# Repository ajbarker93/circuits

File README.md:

# circuits

A repository of printed circuit boards designed using KiCad.

LIAD: a PCB mount for ultra-violet LEDs. Intended use: illumination of a magneto-optical trap chamber to boost vapour pressure.

NI-SCSI: a digitally-isolated breakout for a National Instruments SCSI connector to generate 4x8 data lines for serial communication. Each block of 8 digital lines is combined with a regulated voltage source.

Urukul: a PCB to convert TTL digital signals into LVDS signals for compatibility with the Sinara Urukul DDS board (https://github.com/sinara-hw/Urukul/wiki).

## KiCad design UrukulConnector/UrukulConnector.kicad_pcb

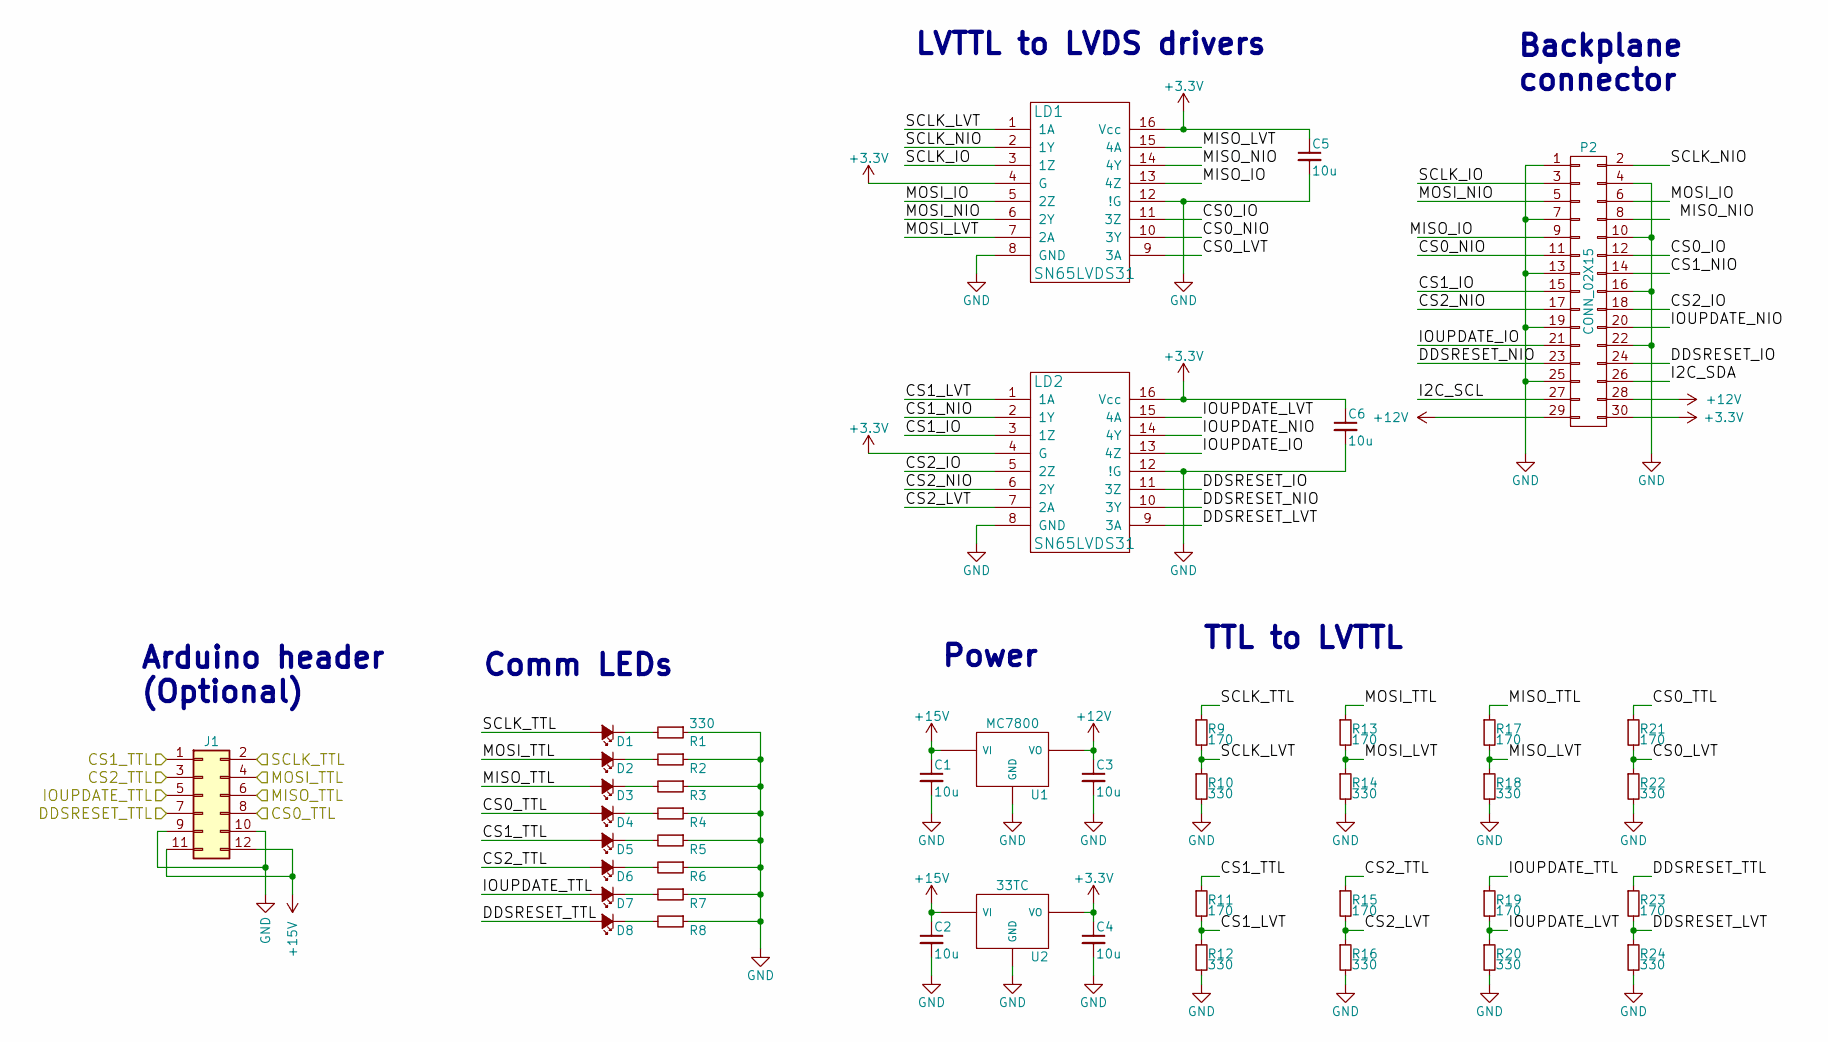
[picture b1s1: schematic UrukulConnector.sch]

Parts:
C1, C2, C3, C4, C5, C6: 10u; C_1206_HandSoldering
D1, D2, D3, D4, D5, D6, D7, D8: Led_Small; R_0805_HandSoldering
J1: Conn_02x06_Odd_Even; Pin_Header_Straight_2x06_Pitch2.54mm
LD1, LD2: SN65LVDS31; SOIC-16_3.9x9.9mm_Pitch1.27mm
P2: CONN_02X15; Pin_Header_Straight_2x15_Pitch2.54mm
R1, R2, R3, R4, R5, R6, R7, R8, R10, R12, R14, R16, R18, R20, R22, R24: 330; R_0805_HandSoldering
R9, R11, R13, R15, R17, R19, R21, R23: 170; R_0805_HandSoldering
U1: MC7800; TO-252-2
U2: 33TC; TO-252-2

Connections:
+3V3: C4.1, C5.1, C6.1, LD1.4 (G), LD1.16 (Vcc), LD2.4 (G), LD2.16 (Vcc), P2.30, U2.2 (VO)
+12V: C3.1, P2.28, P2.29, U1.3 (VO)
+15V: C1.1, C2.1, J1.11, J1.12, U1.1 (VI), U2.3 (VI)
/CS0_IO: LD1.11 (3Z), P2.12
/CS0_LVT: LD1.9 (3A), R21.2, R22.1
/CS0_NIO: LD1.10 (3Y), P2.11
/CS0_TTL: D4.2 (A), J1.8, R21.1
/CS1_IO: LD2.3 (1Z), P2.15
/CS1_LVT: LD2.1 (1A), R11.2, R12.1
/CS1_NIO: LD2.2 (1Y), P2.14
/CS1_TTL: D5.2 (A), J1.1, R11.1
/CS2_IO: LD2.5 (2Z), P2.18
/CS2_LVT: LD2.7 (2A), R15.2, R16.1
/CS2_NIO: LD2.6 (2Y), P2.17
/CS2_TTL: D6.2 (A), J1.3, R15.1
/DDSRESET_IO: LD2.11 (3Z), P2.24
/DDSRESET_LVT: LD2.9 (3A), R23.2, R24.1
/DDSRESET_NIO: LD2.10 (3Y), P2.23
/DDSRESET_TTL: D8.2 (A), J1.7, R23.1
/I2C_SCL: P2.27
/I2C_SDA: P2.26
/IOUPDATE_IO: LD2.13 (4Z), P2.21
/IOUPDATE_LVT: LD2.15 (4A), R19.2, R20.1
/IOUPDATE_NIO: LD2.14 (4Y), P2.20
/IOUPDATE_TTL: D7.2 (A), J1.5, R19.1
/MISO_IO: LD1.13 (4Z)
/MISO_LVT: LD1.15 (4A), R17.2, R18.1
/MISO_NIO: LD1.14 (4Y)
/MISO_TTL: D3.2 (A), J1.6, R17.1
/MOSI_IO: LD1.5 (2Z), P2.6
/MOSI_LVT: LD1.7 (2A), R13.2, R14.1
/MOSI_NIO: LD1.6 (2Y), P2.5
/MOSI_TTL: D2.2 (A), J1.4, R13.1
/SCLK_IO: LD1.3 (1Z), P2.3
/SCLK_LVT: LD1.1 (1A), R9.2, R10.1
/SCLK_NIO: LD1.2 (1Y), P2.2
/SCLK_TTL: D1.2 (A), J1.2, R9.1
GND: C1.2, C2.2, C3.2, C4.2, C5.2, C6.2, J1.9, J1.10, LD1.8 (GND), LD1.12 (!G), LD2.8 (GND), LD2.12 (!G), P2.1, P2.4, P2.7, P2.10, P2.13, P2.16, P2.19, P2.22, P2.25, R1.1, R2.1, R3.1, R4.1, R5.1, R6.1, R7.1, R8.1, R10.2, R12.2, R14.2, R16.2, R18.2, R20.2, R22.2, R24.2, U1.2 (GND), U2.1 (GND)
unnamed: D1.1 (K), R1.2
unnamed: D2.1 (K), R2.2
unnamed: D3.1 (K), R3.2
unnamed: D4.1 (K), R4.2
unnamed: D5.1 (K), R5.2
unnamed: D6.1 (K), R6.2
unnamed: D7.1 (K), R7.2
unnamed: D8.1 (K), R8.2

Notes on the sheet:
Backplane connector
LVTTL to LVDS drivers
Arduino header (Optional)
Power
TTL to LVTTL
Comm LEDs

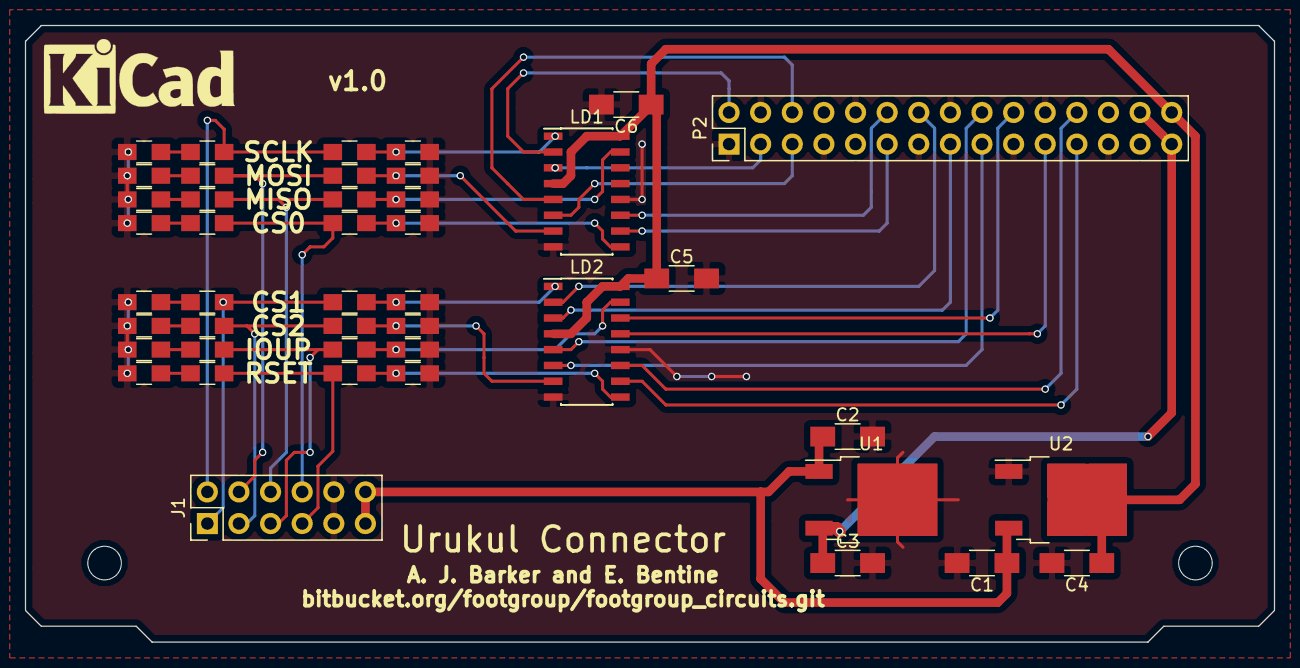
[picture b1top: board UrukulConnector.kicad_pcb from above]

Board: 2 copper layers, 100.3 x 49.5 mm, 44 parts (0 on the bottom side), 42 nets.

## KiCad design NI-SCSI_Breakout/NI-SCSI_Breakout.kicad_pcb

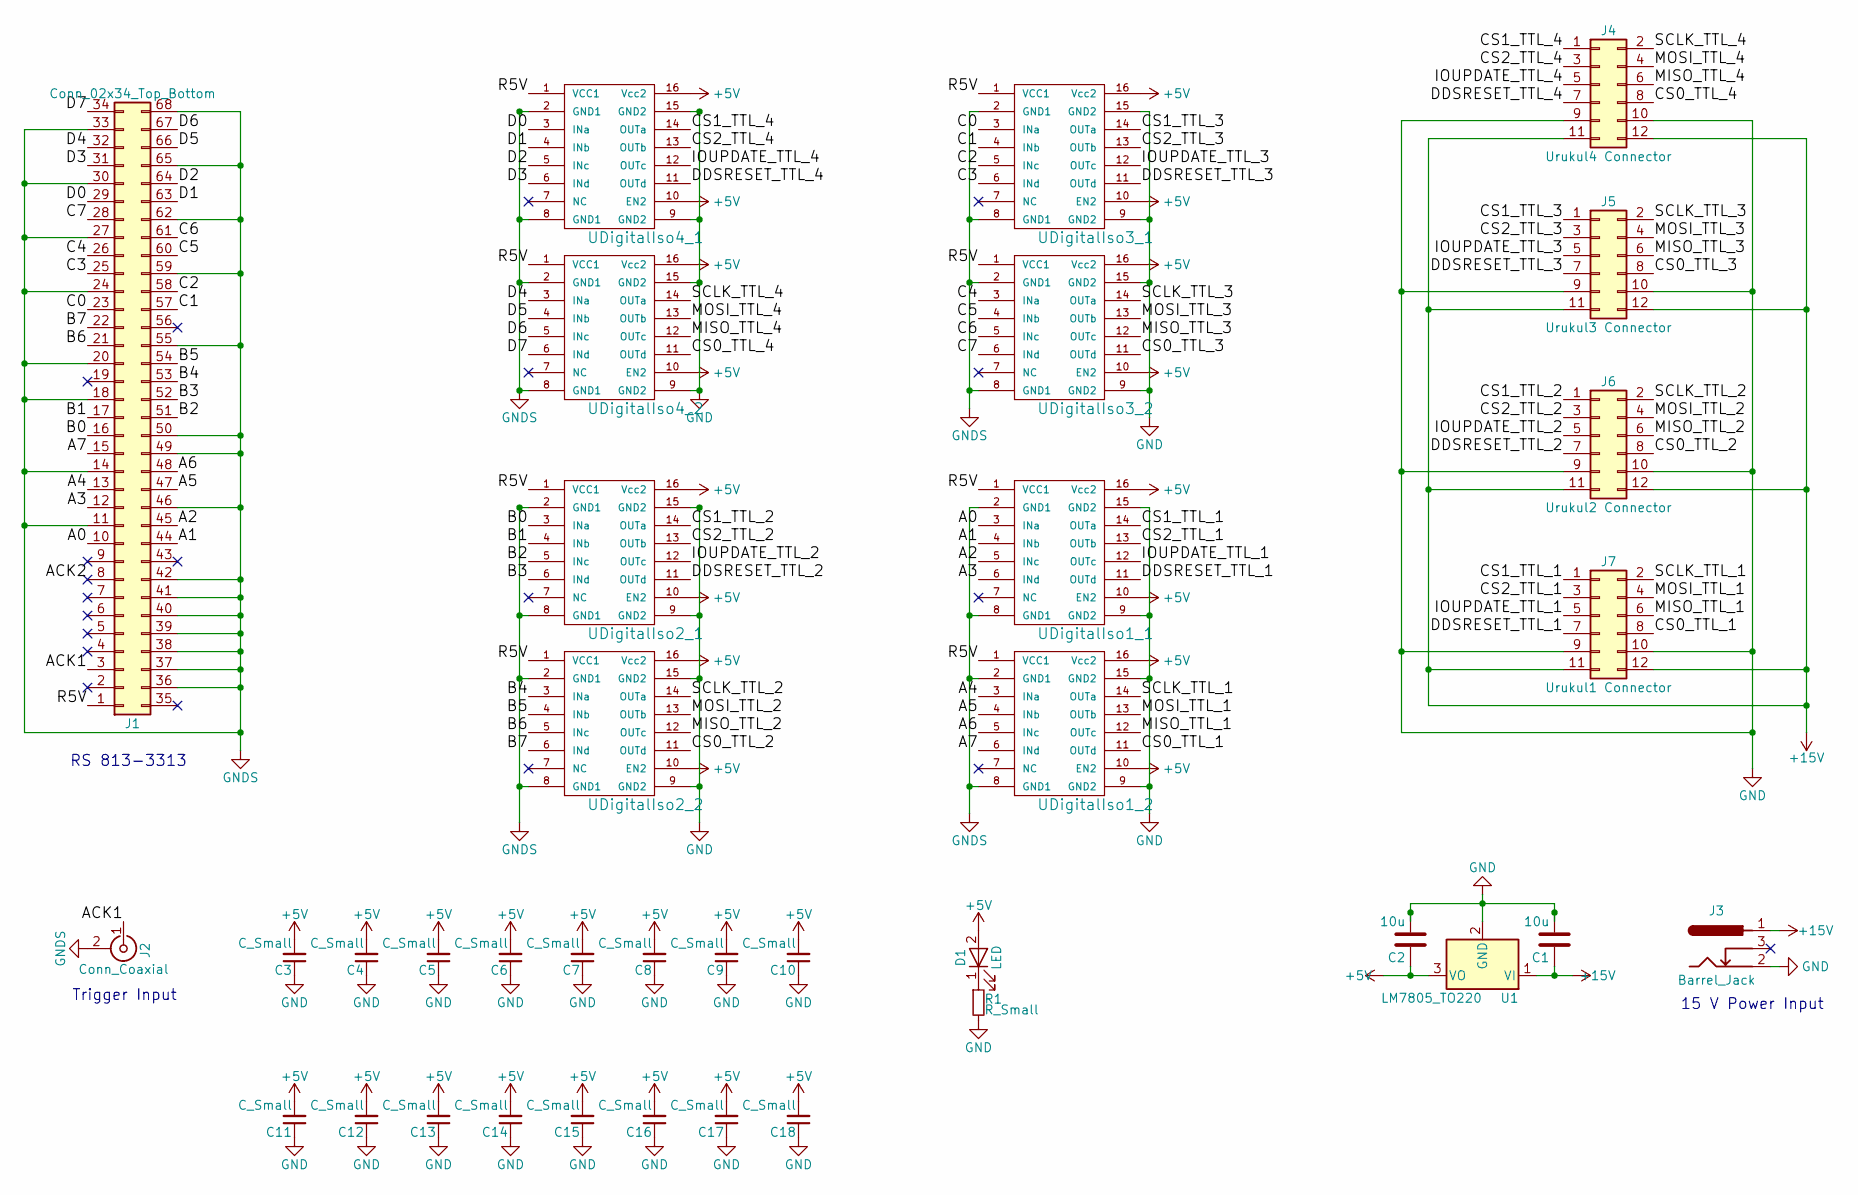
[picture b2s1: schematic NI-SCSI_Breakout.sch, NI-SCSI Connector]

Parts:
C1, C2: 10u; C_0805
C3, C4, C5, C6, C7, C8, C9, C10, C11, C12, C13, C14, C15, C16, C17, C18: C_Small; C_0805_HandSoldering
D1: LED; LED_0805_HandSoldering
J1: Conn_02x34_Top_Bottom; MH_SCSI_68_2.54mm
J2: Conn_Coaxial; SMA_THT_Jack_Straight
J3: Barrel_Jack; Barrel_Jack_CUI_PJ-102AH
J4: Urukul4 Connector; Pin_Header_Straight_2x06_Pitch2.54mm
J5: Urukul3 Connector; Pin_Header_Straight_2x06_Pitch2.54mm
J6: Urukul2 Connector; Pin_Header_Straight_2x06_Pitch2.54mm
J7: Urukul1 Connector; Pin_Header_Straight_2x06_Pitch2.54mm
R1: R_Small; LED_0805_HandSoldering
U1: LM7805_TO220; TO-252-2
UDigitalIso1_1, UDigitalIso1_2, UDigitalIso2_1, UDigitalIso2_2, UDigitalIso3_1, UDigitalIso3_2, UDigitalIso4_1, UDigitalIso4_2: ISO7741FQDWQ1; SOIC-16W_7.5x10.3mm_Pitch1.27mm

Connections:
+5V: C2.1, C3.2, C4.2, C5.2, C6.2, C7.2, C8.2, C9.2, C10.2, C11.2, C12.2, C13.2, C14.2, C15.2, C16.2, C17.2, C18.2, D1.2 (A), U1.3 (VO), UDigitalIso1_1.10 (EN2), UDigitalIso1_1.16 (Vcc2), UDigitalIso1_2.10 (EN2), UDigitalIso1_2.16 (Vcc2), UDigitalIso2_1.10 (EN2), UDigitalIso2_1.16 (Vcc2), UDigitalIso2_2.10 (EN2), UDigitalIso2_2.16 (Vcc2), UDigitalIso3_1.10 (EN2), UDigitalIso3_1.16 (Vcc2), UDigitalIso3_2.10 (EN2), UDigitalIso3_2.16 (Vcc2), UDigitalIso4_1.10 (EN2), UDigitalIso4_1.16 (Vcc2), UDigitalIso4_2.10 (EN2), UDigitalIso4_2.16 (Vcc2)
+15V: C1.1, J3.1, J4.11, J4.12, J5.11, J5.12, J6.11, J6.12, J7.11, J7.12, U1.1 (VI)
/A0: J1.10, UDigitalIso1_1.3 (INa)
/A1: J1.44, UDigitalIso1_1.4 (INb)
/A2: J1.45, UDigitalIso1_1.5 (INc)
/A3: J1.12, UDigitalIso1_1.6 (INd)
/A4: J1.13, UDigitalIso1_2.3 (INa)
/A5: J1.47, UDigitalIso1_2.4 (INb)
/A6: J1.48, UDigitalIso1_2.5 (INc)
/A7: J1.15, UDigitalIso1_2.6 (INd)
/ACK1: J1.3, J2.1 (In)
/ACK2: J1.8
/B0: J1.16, UDigitalIso2_1.3 (INa)
/B1: J1.17, UDigitalIso2_1.4 (INb)
/B2: J1.51, UDigitalIso2_1.5 (INc)
/B3: J1.52, UDigitalIso2_1.6 (INd)
/B4: J1.53, UDigitalIso2_2.3 (INa)
/B5: J1.54, UDigitalIso2_2.4 (INb)
/B6: J1.21, UDigitalIso2_2.5 (INc)
/B7: J1.22, UDigitalIso2_2.6 (INd)
/C0: J1.23, UDigitalIso3_1.3 (INa)
/C1: J1.57, UDigitalIso3_1.4 (INb)
/C2: J1.58, UDigitalIso3_1.5 (INc)
/C3: J1.25, UDigitalIso3_1.6 (INd)
/C4: J1.26, UDigitalIso3_2.3 (INa)
/C5: J1.60, UDigitalIso3_2.4 (INb)
/C6: J1.61, UDigitalIso3_2.5 (INc)
/C7: J1.28, UDigitalIso3_2.6 (INd)
/CS0_TTL_1: J7.8, UDigitalIso1_2.11 (OUTd)
/CS0_TTL_2: J6.8, UDigitalIso2_2.11 (OUTd)
/CS0_TTL_3: J5.8, UDigitalIso3_2.11 (OUTd)
/CS0_TTL_4: J4.8, UDigitalIso4_2.11 (OUTd)
/CS1_TTL_1: J7.1, UDigitalIso1_1.14 (OUTa)
/CS1_TTL_2: J6.1, UDigitalIso2_1.14 (OUTa)
/CS1_TTL_3: J5.1, UDigitalIso3_1.14 (OUTa)
/CS1_TTL_4: J4.1, UDigitalIso4_1.14 (OUTa)
/CS2_TTL_1: J7.3, UDigitalIso1_1.13 (OUTb)
/CS2_TTL_2: J6.3, UDigitalIso2_1.13 (OUTb)
/CS2_TTL_3: J5.3, UDigitalIso3_1.13 (OUTb)
/CS2_TTL_4: J4.3, UDigitalIso4_1.13 (OUTb)
/D0: J1.29, UDigitalIso4_1.3 (INa)
/D1: J1.63, UDigitalIso4_1.4 (INb)
/D2: J1.64, UDigitalIso4_1.5 (INc)
/D3: J1.31, UDigitalIso4_1.6 (INd)
/D4: J1.32, UDigitalIso4_2.3 (INa)
/D5: J1.66, UDigitalIso4_2.4 (INb)
/D6: J1.67, UDigitalIso4_2.5 (INc)
/D7: J1.34, UDigitalIso4_2.6 (INd)
/DDSRESET_TTL_1: J7.7, UDigitalIso1_1.11 (OUTd)
/DDSRESET_TTL_2: J6.7, UDigitalIso2_1.11 (OUTd)
/DDSRESET_TTL_3: J5.7, UDigitalIso3_1.11 (OUTd)
/DDSRESET_TTL_4: J4.7, UDigitalIso4_1.11 (OUTd)
/IOUPDATE_TTL_1: J7.5, UDigitalIso1_1.12 (OUTc)
/IOUPDATE_TTL_2: J6.5, UDigitalIso2_1.12 (OUTc)
/IOUPDATE_TTL_3: J5.5, UDigitalIso3_1.12 (OUTc)
/IOUPDATE_TTL_4: J4.5, UDigitalIso4_1.12 (OUTc)
/MISO_TTL_1: J7.6, UDigitalIso1_2.12 (OUTc)
/MISO_TTL_2: J6.6, UDigitalIso2_2.12 (OUTc)
/MISO_TTL_3: J5.6, UDigitalIso3_2.12 (OUTc)
/MISO_TTL_4: J4.6, UDigitalIso4_2.12 (OUTc)
/MOSI_TTL_1: J7.4, UDigitalIso1_2.13 (OUTb)
/MOSI_TTL_2: J6.4, UDigitalIso2_2.13 (OUTb)
/MOSI_TTL_3: J5.4, UDigitalIso3_2.13 (OUTb)
/MOSI_TTL_4: J4.4, UDigitalIso4_2.13 (OUTb)
/R5V: J1.1, UDigitalIso1_1.1 (VCC1), UDigitalIso1_2.1 (VCC1), UDigitalIso2_1.1 (VCC1), UDigitalIso2_2.1 (VCC1), UDigitalIso3_1.1 (VCC1), UDigitalIso3_2.1 (VCC1), UDigitalIso4_1.1 (VCC1), UDigitalIso4_2.1 (VCC1)
/SCLK_TTL_1: J7.2, UDigitalIso1_2.14 (OUTa)
/SCLK_TTL_2: J6.2, UDigitalIso2_2.14 (OUTa)
/SCLK_TTL_3: J5.2, UDigitalIso3_2.14 (OUTa)
/SCLK_TTL_4: J4.2, UDigitalIso4_2.14 (OUTa)
GND: C1.2, C2.2, C3.1, C4.1, C5.1, C6.1, C7.1, C8.1, C9.1, C10.1, C11.1, C12.1, C13.1, C14.1, C15.1, C16.1, C17.1, C18.1, J3.2, J4.9, J4.10, J5.9, J5.10, J6.9, J6.10, J7.9, J7.10, R1.2, U1.2 (GND), UDigitalIso1_1.9 (GND2), UDigitalIso1_1.15 (GND2), UDigitalIso1_2.9 (GND2), UDigitalIso1_2.15 (GND2), UDigitalIso2_1.9 (GND2), UDigitalIso2_1.15 (GND2), UDigitalIso2_2.9 (GND2), UDigitalIso2_2.15 (GND2), UDigitalIso3_1.9 (GND2), UDigitalIso3_1.15 (GND2), UDigitalIso3_2.9 (GND2), UDigitalIso3_2.15 (GND2), UDigitalIso4_1.9 (GND2), UDigitalIso4_1.15 (GND2), UDigitalIso4_2.9 (GND2), UDigitalIso4_2.15 (GND2)
GNDS: J1.11, J1.14, J1.18, J1.20, J1.24, J1.27, J1.30, J1.33, J1.36, J1.37, J1.38, J1.39, J1.40, J1.41, J1.42, J1.46, J1.49, J1.50, J1.55, J1.59, J1.62, J1.65, J1.68, J2.2 (Ext), UDigitalIso1_1.2 (GND1), UDigitalIso1_1.8 (GND1), UDigitalIso1_2.2 (GND1), UDigitalIso1_2.8 (GND1), UDigitalIso2_1.2 (GND1), UDigitalIso2_1.8 (GND1), UDigitalIso2_2.2 (GND1), UDigitalIso2_2.8 (GND1), UDigitalIso3_1.2 (GND1), UDigitalIso3_1.8 (GND1), UDigitalIso3_2.2 (GND1), UDigitalIso3_2.8 (GND1), UDigitalIso4_1.2 (GND1), UDigitalIso4_1.8 (GND1), UDigitalIso4_2.2 (GND1), UDigitalIso4_2.8 (GND1)
unnamed: D1.1 (K), R1.1

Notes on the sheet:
RS 813-3313
Trigger Input
15 V Power Input

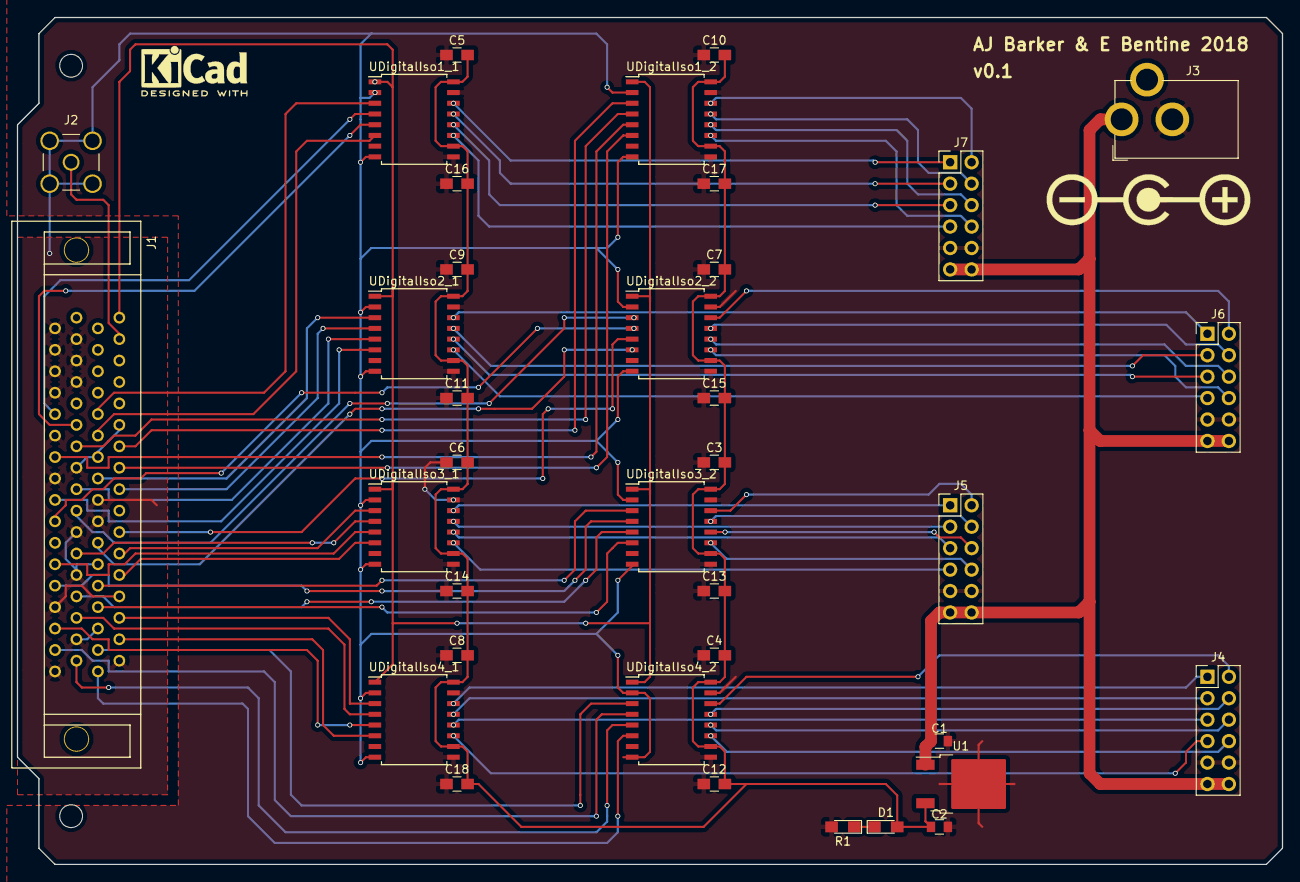
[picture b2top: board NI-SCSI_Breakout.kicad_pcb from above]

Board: 2 copper layers, 149.9 x 100.3 mm, 36 parts (0 on the bottom side), 71 nets.

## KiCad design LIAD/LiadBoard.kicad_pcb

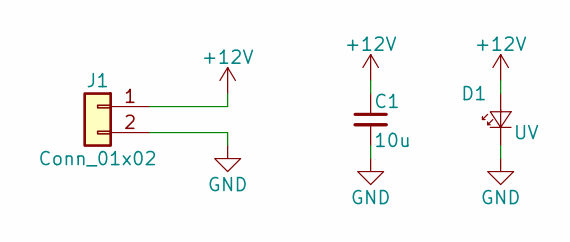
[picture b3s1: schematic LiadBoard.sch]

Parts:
C1: 10u; C_0805_HandSoldering
D1: UV; 890-3954
J1: Conn_01x02; Pin_Header_Straight_1x02_Pitch2.54mm

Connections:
+12V: C1.1, D1.2 (A), J1.1
GND: C1.2, D1.1 (K), J1.2

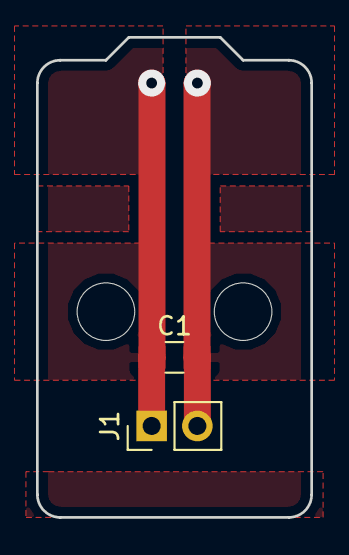
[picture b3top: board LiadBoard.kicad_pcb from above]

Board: 2 copper layers, 15.2 x 26.7 mm, 3 parts (1 on the bottom side), 2 nets.

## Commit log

2020-02-05 Create README.md
    Added readMe for circuit descriptions and intended use cases.
